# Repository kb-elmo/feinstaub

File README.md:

# Feinstaub

[![CC BY-SA 4.0][cc-by-sa-shield]][cc-by-sa]

## This project is completed and will not get updated anymore.

### ESP-12F powered piggyback PCB for the SDS011 fine dust sensor

The board is designed to run with the luftdaten.info firmware and has a place for a BME280 sensor.

Pic of the prototype (with enamel wire because it wouldn't be a prototype without it).

---

### BOM
 |Count|Part|Reference|Part URL|
 |-|-|-|-|
 |1|ESP12-F|U1|[ESP-12F](https://www.ebay.de/itm/255303527301)
 |1|Bosch BME-280 module|U2|[BME280](https://www.ebay.de/itm/255421634848)
 |1|Nova Fitness SDS-011 Module|---|[SDS-011](https://www.ebay.de/itm/255283289438)
 |1|AMS1117-3.3v step-down module|U3|[AMS1117-3.3 module](https://www.ebay.de/itm/174076431478)
 |1|DIP switch|SW1|[DIP-Switch](https://www.ebay.de/itm/255421634848)
 |1|100 nF ceramic disk capacitor|C1|[Kemet C315C104M5U5TA](https://octopart.com/c315c104m5u5ta-kemet-83288)
 |4|10 kΩ resistor|R1-R4|[Multicomp MF25 10k](https://octopart.com/mf25+10k-multicomp-2697429)

#### Assembly notes
The SDS011 module gets connected to the J2 pins on the main PCB.  
Remember that TX and RX have to be connected in reverse on the module.

The ESP chip can be flashed by connecting an ISP flasher to the J1 pins.  
To put the chip into flashing mode set the boot switch to on, plug in the power and then turn the switch back off.  
The easiest method of flashing the chip is by using the [AirRohr firmware updater](https://github.com/opendata-stuttgart/airrohr-firmware-flasher)

For the main power input a 5v / 0.5-1A power supply should be used.

DO NOT CONNECT BOTH THE MAIN POWER AND A USB FLASHER WITH POWER INPUT AT ONCE!!!  
If you use a flashing device that has 3.3v power output on it's own the main power has to be left unconnected.

---

---

This work is licensed under a
[Creative Commons Attribution-ShareAlike 4.0 International License][cc-by-sa].

[![CC BY-SA 4.0][cc-by-sa-image]][cc-by-sa]

[cc-by-sa]: http://creativecommons.org/licenses/by-sa/4.0/
[cc-by-sa-image]: https://licensebuttons.net/l/by-sa/4.0/88x31.png
[cc-by-sa-shield]: https://img.shields.io/badge/License-CC%20BY--SA%204.0-lightgrey.svg

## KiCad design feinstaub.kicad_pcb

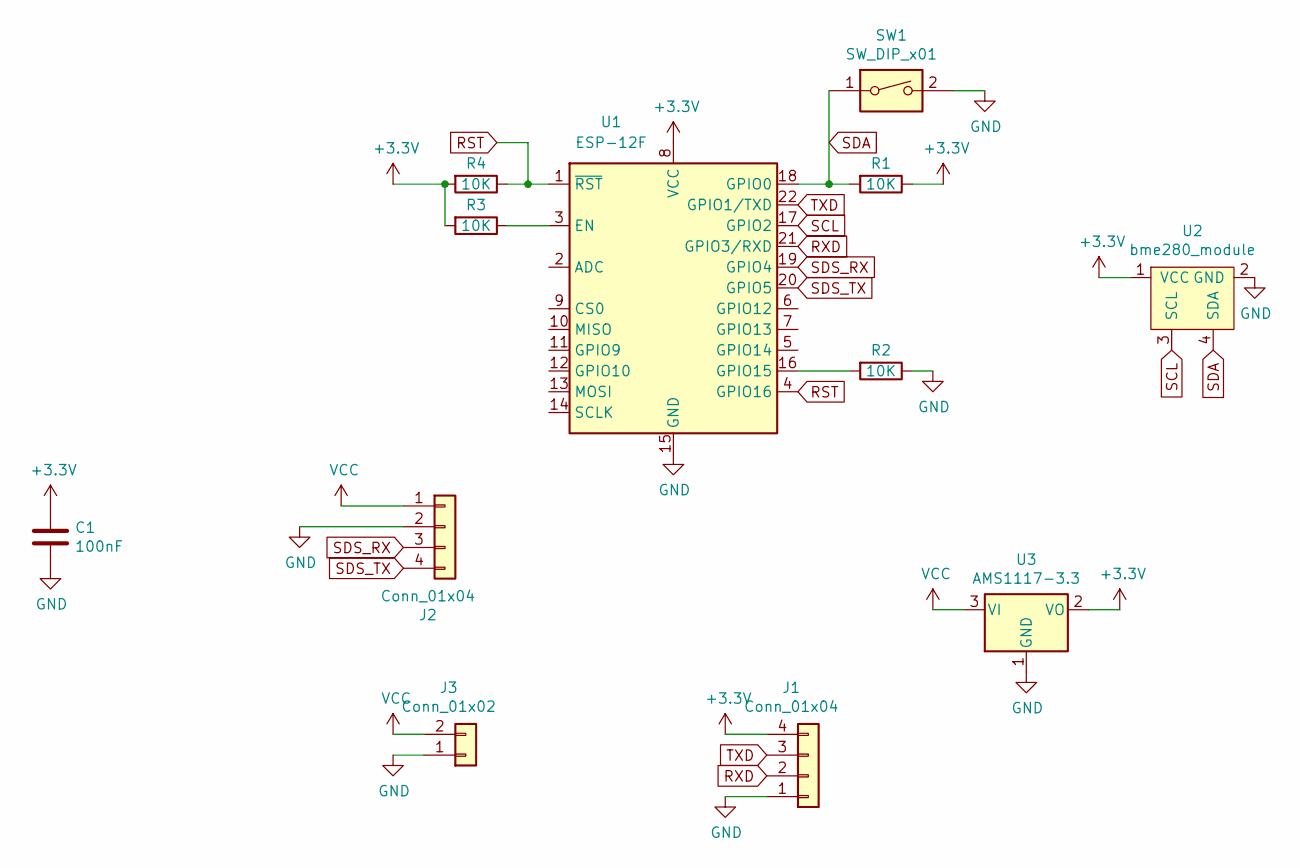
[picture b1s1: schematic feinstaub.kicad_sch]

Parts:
C1: 100nF; C_Disc_D5.0mm_W2.5mm_P2.50mm
J1, J2: Conn_01x04; PinHeader_1x04_P2.54mm_Vertical
J3: Conn_01x02; PinHeader_1x02_P2.54mm_Horizontal
R1, R2, R3, R4: 10K; R_Axial_DIN0207_L6.3mm_D2.5mm_P10.16mm_Horizontal
SW1: SW_DIP_x01; SW_DIP_SPSTx01_Slide_9.78x4.72mm_W7.62mm_P2.54mm
U1: ESP-12F
U2: bme280_module; bme280
U3: AMS1117-3.3; PinSocket_1x03_P2.54mm_Vertical

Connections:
+3V3: C1.1, J1.4, R1.1, R3.2, R4.2, U1.8 (VCC), U2.1 (VCC), U3.2 (VO)
GND: C1.2, J1.1, J2.2, J3.1, R2.1, SW1.2, U1.15 (GND), U2.2 (GND), U3.1 (GND)
unnamed: R2.2, U1.16 (GPIO15)
unnamed: R3.1, U1.3 (EN)
RST: R4.1, U1.1 (~RST), U1.4 (GPIO16)
RXD: J1.2, U1.21 (GPIO3/RXD)
SCL: U1.17 (GPIO2), U2.3 (SCL)
SDA: R1.2, SW1.1, U1.18 (GPIO0), U2.4 (SDA)
SDS_RX: J2.3, U1.19 (GPIO4)
SDS_TX: J2.4, U1.20 (GPIO5)
TXD: J1.3, U1.22 (GPIO1/TXD)
VCC: J2.1, J3.2, U3.3 (VI)

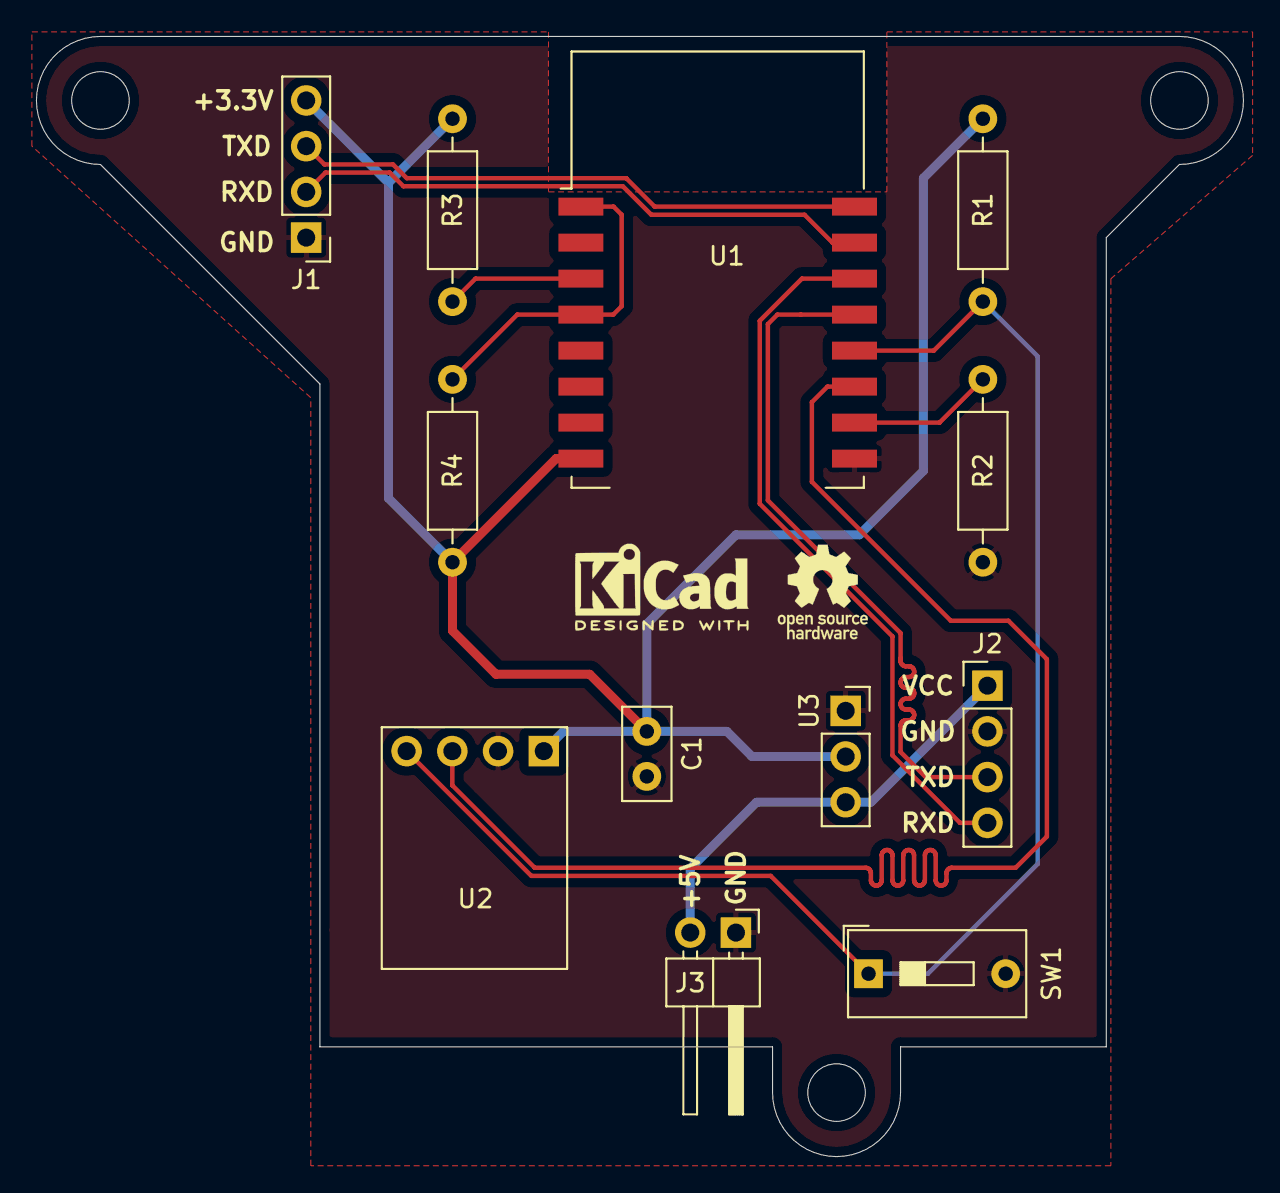
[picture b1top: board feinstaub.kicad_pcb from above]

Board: 2 copper layers, 67.1 x 62.2 mm, 12 parts (0 on the bottom side), 12 nets.

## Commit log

2021-08-16 Create LICENSE
2022-05-05 small update
